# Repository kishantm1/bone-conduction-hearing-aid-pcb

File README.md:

# Wearable Bone Conduction Hearing Aid / Headphone PCB  

Wearable bone-conduction hearing aid headphone PCB based on the ESP32-S3, integrating an I2S MEMS microphone input, I2S audio amplifier output, LiPo battery charging, USB-C power/programming support, and a bone-conduction transducer interface. This project focused on end-to-end wearable audio hardware development, including BOM creation, schematic design, PCB layout, and board assembly through JLCPCB. 

## Key Features

- Wearable headphone / hearing aid form factor
- ESP32-S3-based embedded audio platform
- I2S MEMS microphone input for audio capture
- I2S DAC/amplifier output for driving a bone-conduction transducer
- 3.7V battery-powered design

## Hardware Architecture

The board is centered around the ESP32-S3 microcontroller and integrates audio input, audio output, battery charging, power regulation, and programming/debug circuitry into a compact wearable PCB.

- **MCU:** ESP32-S3-WROOM-1
- **Microphone input:** I2S MEMS microphone for audio capture
- **Audio output:** I2S DAC/amplifier for driving the bone-conduction transducer
- **Transducer interface:** 2-pin connector for bone-conduction transducer output
- **Power:** 3.7V LiPo battery with USB-C charging and regulated 3.3V system power
- **Debug/programming:** Boot and reset support circuitry
- **Indicators:** Status LED for board/charging indication

## Schematic

### Power

### Processor

### Audio

## Layout

The 2-layer PCB layout was designed to fit the audio input/output, power, charging, and programming circuitry into a compact wearable form factor.

## 3D View

## Assembled Board

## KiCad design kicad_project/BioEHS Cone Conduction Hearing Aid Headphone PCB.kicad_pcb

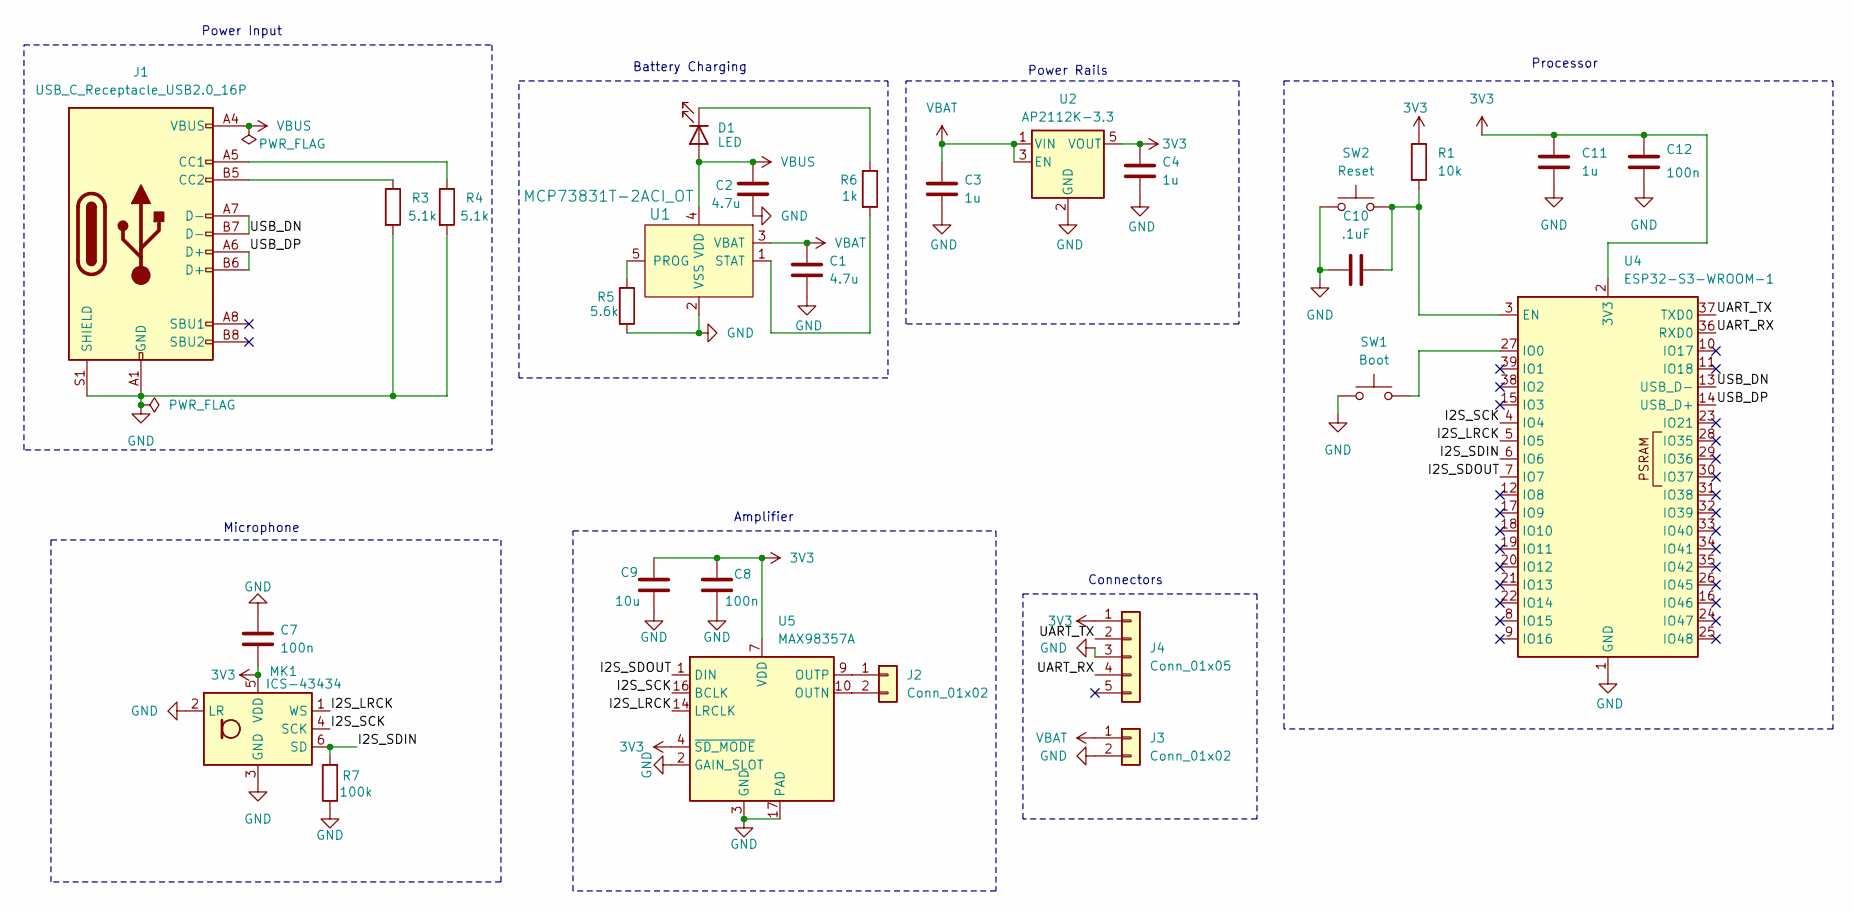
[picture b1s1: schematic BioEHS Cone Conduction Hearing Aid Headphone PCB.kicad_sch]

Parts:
C1, C2: 4.7u; C_0402_1005Metric
C3, C4, C11: 1u; C_0603_1608Metric
C7, C8, C12: 100n; C_0402_1005Metric
C9: 10u; C_0603_1608Metric
C10: .1uF; C_0402_1005Metric
D1: LED; LED_0805_2012Metric
J1: USB_C_Receptacle_USB2.0_16P; USB_C_Receptacle_GCT_USB4085
J2: Conn_01x02; JST_SH_BM02B-SRSS-TB_1x02-1MP_P1.00mm_Vertical
J3: Conn_01x02; JST_PH_S2B-PH-K_1x02_P2.00mm_Horizontal
J4: Conn_01x05; PinHeader_1x05_P1.27mm_Vertical
MK1: ICS-43434; InvenSense_ICS-43434-6_3.5x2.65mm
R1: 10k; R_0402_1005Metric
R3, R4: 5.1k; R_0402_1005Metric
R5: 5.6k; R_0402_1005Metric
R6: 1k; R_0402_1005Metric
R7: 100k; R_0402_1005Metric
SW1: Boot; SW_Push_1P1T-SH_NO_CK_KMR2xxG
SW2: Reset; SW_Push_1P1T-SH_NO_CK_KMR2xxG
U1: MCP73831T-2ACI_OT; SOT-23-5; MPN MCP73831T-2ACI/OT; Digi-Key_PN MCP73831T-2ACI/OTCT-ND
U2: AP2112K-3.3; SOT-23-5
U4: ESP32-S3-WROOM-1
U5: MAX98357A; TQFN-16-1EP_3x3mm_P0.5mm_EP1.23x1.23mm

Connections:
3V3: C4.1, C7.2, C8.1, C9.1, C11.1, C12.1, J4.1, MK1.5 (VDD), R1.1, U2.5 (VOUT), U4.2 (3V3), U5.4 (~SD_MODE), U5.7 (VDD), U5.8 (VDD)
/I2S_LRCK: MK1.1 (WS), U4.5 (IO5), U5.14 (LRCLK)
/I2S_SCK: MK1.4 (SCK), U4.4 (IO4), U5.16 (BCLK)
/I2S_SDIN: MK1.6 (SD), R7.2, U4.6 (IO6)
/I2S_SDOUT: U4.7 (IO7), U5.1 (DIN)
/UART_RX: J4.4, U4.36 (RXD0)
/UART_TX: J4.2, U4.37 (TXD0)
/USB_DN: J1.A7 (D-), J1.B7 (D-), U4.13 (USB_D-)
/USB_DP: J1.A6 (D+), J1.B6 (D+), U4.14 (USB_D+)
GND: C1.2, C2.2, C3.2, C4.2, C7.1, C8.2, C9.2, C10.1, C11.2, C12.2, J1.A1 (GND), J1.A12 (GND), J1.B1 (GND), J1.B12 (GND), J1.S1 (SHIELD), J3.2, J4.3, MK1.2 (LR), MK1.3 (GND), R3.2, R4.2, R5.2, R7.1, SW1.2, SW2.1, U1.2 (VSS), U2.2 (GND), U4.1 (GND), U4.40 (GND), U4.41 (GND), U5.2 (GAIN_SLOT), U5.3 (GND), U5.11 (GND), U5.15 (GND), U5.17 (PAD)
unnamed: D1.1 (K), R6.1
unnamed: J1.A5 (CC1), R4.1
unnamed: J1.B5 (CC2), R3.1
unnamed: J2.1, U5.9 (OUTP)
unnamed: J2.2, U5.10 (OUTN)
unnamed: R5.1, U1.5 (PROG)
unnamed: R6.2, U1.1 (STAT)
unnamed: C10.2, R1.2, SW2.2, U4.3 (EN)
unnamed: SW1.1, U4.27 (IO0)
VBAT: C1.1, C3.1, J3.1, U1.3 (VBAT), U2.1 (VIN), U2.3 (EN)
VBUS: C2.1, D1.2 (A), J1.A4 (VBUS), J1.A9 (VBUS), J1.B4 (VBUS), J1.B9 (VBUS), U1.4 (VDD)

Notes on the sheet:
Battery Charging
Microphone
Power Rails
Amplifier
Power Input
Connectors
Processor

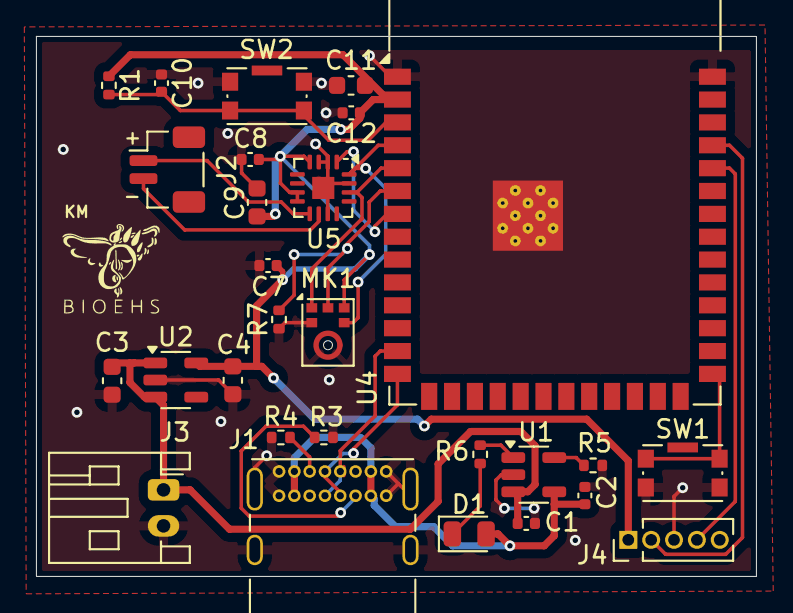
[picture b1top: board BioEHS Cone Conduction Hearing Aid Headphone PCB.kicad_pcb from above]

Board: 2 copper layers, 40.0 x 30.0 mm, 28 parts (0 on the bottom side), 21 nets.

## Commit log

2026-06-24 Bone Conduction Images
2026-06-24 Bone Conduction Board Images
2026-06-24 Create kicad_project
2026-06-24 Library.pretty
2026-06-24 KiCad Files
